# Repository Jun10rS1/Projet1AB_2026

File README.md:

# Projet1AB_2026
Notre projet comptage de personne

## Pense bete Git

```bash
git pull
# travail travail travail
git status
git add .
git commit -m "texte intelligent"
git push
```

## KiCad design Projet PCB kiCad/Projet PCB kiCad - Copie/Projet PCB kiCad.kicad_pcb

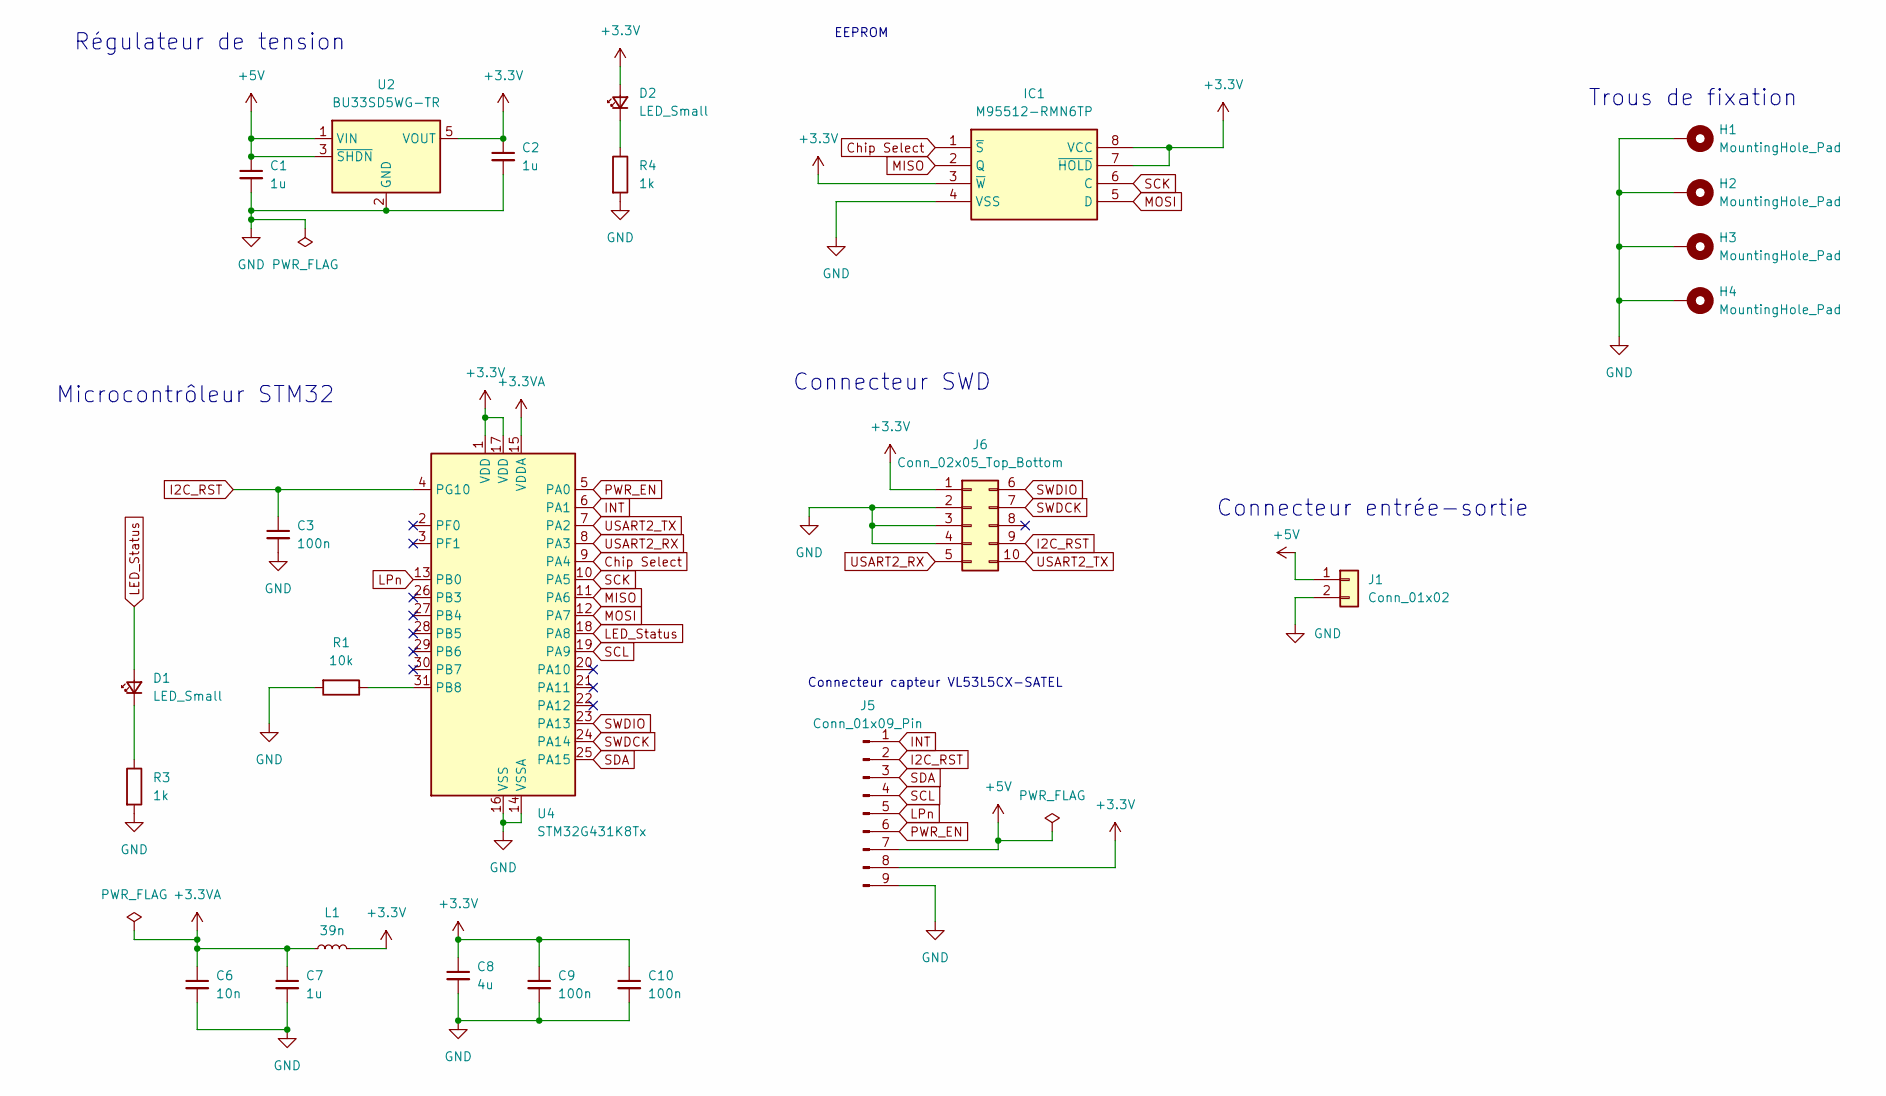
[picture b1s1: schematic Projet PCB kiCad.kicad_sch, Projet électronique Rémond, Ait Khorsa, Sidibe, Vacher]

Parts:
C1, C2, C7: 1u; C_0603_1608Metric_Pad1.08x0.95mm_HandSolder
C3, C9, C10: 100n; C_0603_1608Metric_Pad1.08x0.95mm_HandSolder
C6: 10n; C_0603_1608Metric_Pad1.08x0.95mm_HandSolder
C8: 4u; C_0603_1608Metric_Pad1.08x0.95mm_HandSolder
D1, D2: LED_Small; LED_0402_1005Metric_Pad0.77x0.64mm_HandSolder
H1, H2, H3, H4: MountingHole_Pad; MountingHole_3.2mm_M3_DIN965_Pad
IC1: M95512-RMN6TP; SOIC-8_3.9x4.9mm_P1.27mm; Mouser Part Number 511-M95512-RMN6TP
J1: Conn_01x02; JST_XH_B2B-XH-A_1x02_P2.50mm_Vertical
J5: Conn_01x09_Pin; PinSocket_1x09_P2.54mm_Vertical
J6: Conn_02x05_Top_Bottom; PinHeader_2x05_P2.54mm_Vertical
L1: 39n; L_0805_2012Metric_Pad1.05x1.20mm_HandSolder
R1: 10k; R_0402_1005Metric_Pad0.72x0.64mm_HandSolder
R3, R4: 1k; R_0402_1005Metric_Pad0.72x0.64mm_HandSolder
U2: BU33SD5WG-TR; SOT-23-5
U4: STM32G431K8Tx; LQFP-32_7x7mm_P0.8mm

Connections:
+3.3V: C2.1, C8.1, C9.1, C10.1, D2.2 (A), IC1.3 (~W), IC1.7 (~HOLD), IC1.8 (VCC), J5.8, J6.1, L1.2, U2.5 (VOUT), U4.1 (VDD), U4.17 (VDD)
+3.3VA: C6.1, C7.1, L1.1, U4.15 (VDDA)
+5V: C1.1, J1.1, J5.7, U2.1 (VIN), U2.3 (~SHDN)
Chip Select: IC1.1 (~S), U4.9 (PA4)
GND: C1.2, C2.2, C3.2, C6.2, C7.2, C8.2, C9.2, C10.2, H1.1, H2.1, H3.1, H4.1, IC1.4 (VSS), J1.2, J5.9, J6.2, J6.3, J6.4, R1.2, R3.2, R4.2, U2.2 (GND), U4.14 (VSSA), U4.16 (VSS), U4.32 (VSS)
I2C_RST: C3.1, J5.2, J6.9, U4.4 (PG10)
INT: J5.1, U4.6 (PA1)
LED_Status: D1.2 (A), U4.18 (PA8)
LPn: J5.5, U4.13 (PB0)
MISO: IC1.2 (Q), U4.11 (PA6)
MOSI: IC1.5 (D), U4.12 (PA7)
unnamed: D1.1 (K), R3.1
unnamed: D2.1 (K), R4.1
unnamed: R1.1, U4.31 (PB8)
PWR_EN: J5.6, U4.5 (PA0)
SCK: IC1.6 (C), U4.10 (PA5)
SCL: J5.4, U4.19 (PA9)
SDA: J5.3, U4.25 (PA15)
SWDCK: J6.7, U4.24 (PA14)
SWDIO: J6.6, U4.23 (PA13)
USART2_RX: J6.5, U4.8 (PA3)
USART2_TX: J6.10, U4.7 (PA2)

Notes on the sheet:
Trous de fixation
Connecteur entrée-sortie
Microcontrôleur STM32
Connecteur SWD
Régulateur de tension
EEPROM
Connecteur capteur VL53L5CX-SATEL

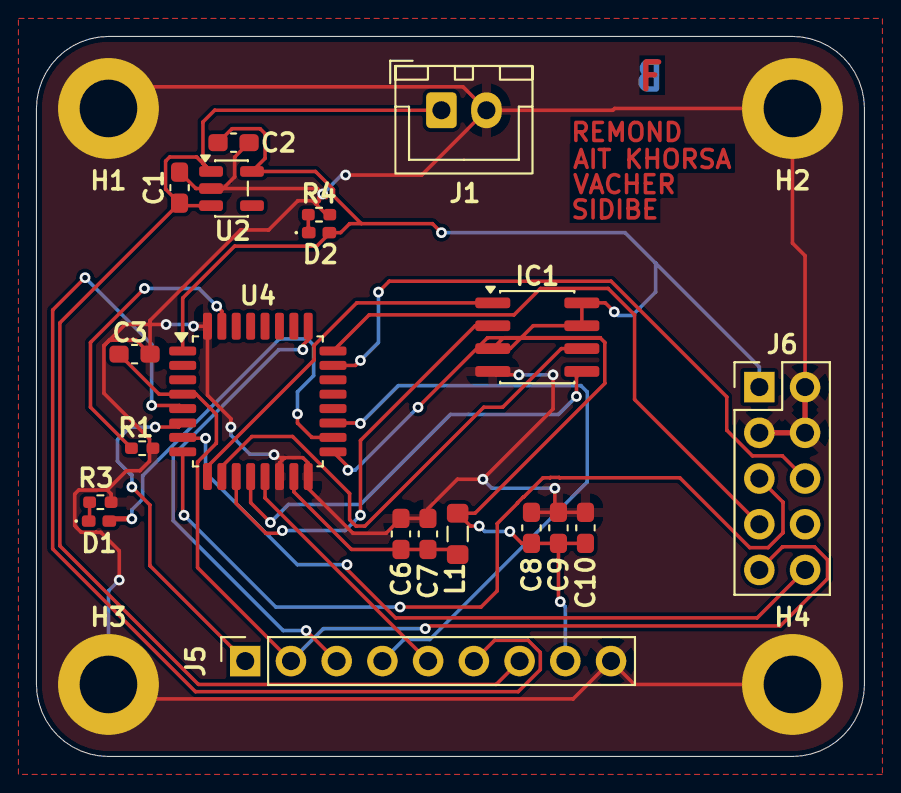
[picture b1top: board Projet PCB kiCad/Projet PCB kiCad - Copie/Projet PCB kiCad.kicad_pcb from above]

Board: 4 copper layers, 46.0 x 40.0 mm, 24 parts (0 on the bottom side), 22 nets.

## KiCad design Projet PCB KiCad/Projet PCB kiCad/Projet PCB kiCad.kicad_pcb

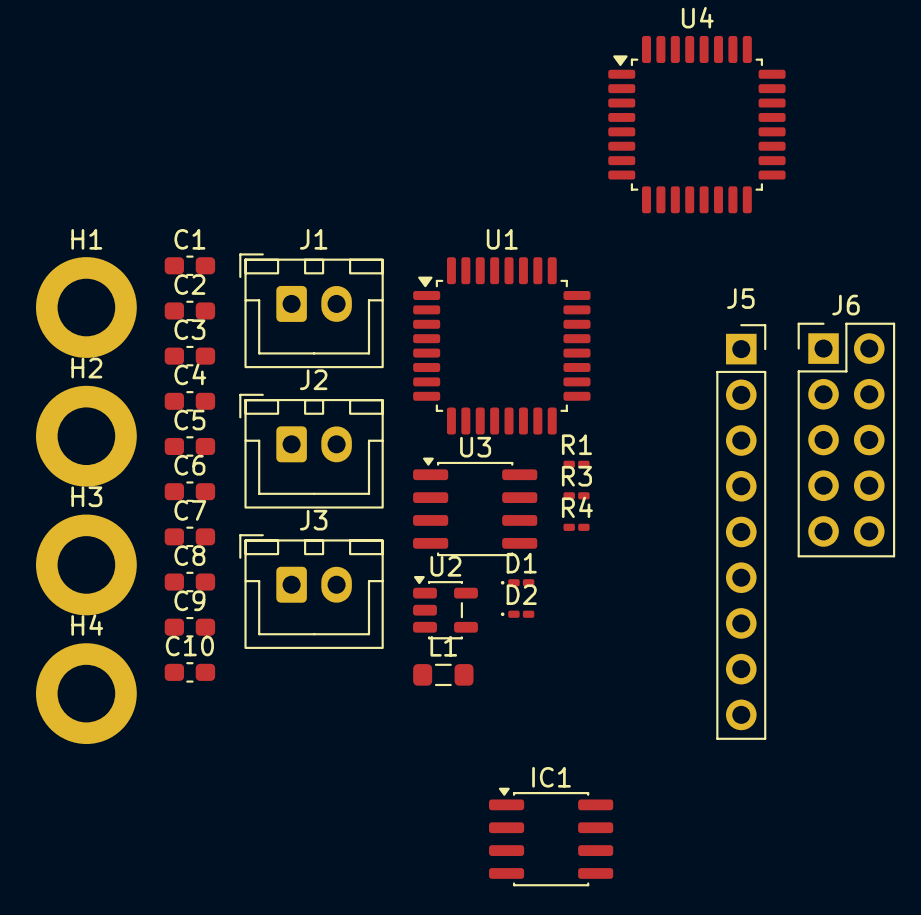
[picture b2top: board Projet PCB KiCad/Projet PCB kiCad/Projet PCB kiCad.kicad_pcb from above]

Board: 2 copper layers, 30 parts (0 on the bottom side), 19 nets, no tracks yet.

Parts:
C1, C2, C7: 1u; C_0603_1608Metric_Pad1.08x0.95mm_HandSolder
C3, C4, C9, C10: 100n; C_0603_1608Metric_Pad1.08x0.95mm_HandSolder
C5: 10u; C_0603_1608Metric_Pad1.08x0.95mm_HandSolder
C6: 10n; C_0603_1608Metric_Pad1.08x0.95mm_HandSolder
C8: 4u; C_0603_1608Metric_Pad1.08x0.95mm_HandSolder
D1, D2: LED_Small; LED_0201_0603Metric_Pad0.64x0.40mm_HandSolder
H1, H2, H3, H4: MountingHole_Pad; MountingHole_3.2mm_M3_DIN965_Pad
IC1: M95512-RMN6TP; SOIC-8_3.9x4.9mm_P1.27mm
J1, J2, J3: Conn_01x02; JST_XH_B2B-XH-A_1x02_P2.50mm_Vertical
J5: Conn_01x09_Pin; PinSocket_1x09_P2.54mm_Vertical
J6: Conn_02x05_Top_Bottom; PinHeader_2x05_P2.54mm_Vertical
L1: 39n; L_0805_2012Metric_Pad1.05x1.20mm_HandSolder
R1: 10k; R_0201_0603Metric_Pad0.64x0.40mm_HandSolder
R3, R4: 1k; R_0201_0603Metric_Pad0.64x0.40mm_HandSolder
U1: STM32L021K4Tx; LQFP-32_7x7mm_P0.8mm
U2: BU33SD5WG-TR; SOT-23-5
U3: MCP4801; SOIC-8_3.9x4.9mm_P1.27mm
U4: STM32G431K8Tx; LQFP-32_7x7mm_P0.8mm

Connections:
+3.3V: C2.1, C8.1, C9.1, C10.1, D2.2 (A), J6.1, L1.2, U1.1 (VDD), U1.17 (VDD), U2.5 (VOUT), U4.1 (VDD), U4.17 (VDD)
+3.3VA: C4.1, C5.1, C6.1, C7.1, L1.1, U1.5 (VDDA), U3.1 (Vdd), U3.6 (~SHDN), U4.15 (VDDA)
+5V: C1.1, J1.1, U2.1 (VIN), U2.3 (~SHDN)
ADC_IN1: J2.1, U1.7 (PA1), U4.6 (PA1)
DAC_OUT: J3.1, U3.8 (Vout)
DAC_nCS: U1.10 (PA4), U3.2 (~CS)
DAC_nLDAC: U1.9 (PA3), U3.5 (~LDAC)
GND: C1.2, C2.2, C3.2, C4.2, C5.2, C6.2, C7.2, C8.2, C9.2, C10.2, H1.1, H2.1, H3.1, H4.1, J1.2, J2.2, J3.2, J5.9, J6.2, J6.3, J6.4, R1.2, R3.2, R4.2, U1.16 (VSS), U1.32 (VSS), U2.2 (GND), U3.7 (Vss), U4.14 (VSSA), U4.16 (VSS), U4.32 (VSS)
LED_Status: D1.2 (A), U1.18 (PA8), U4.18 (PA8)
unnamed: D1.1 (K), R3.1
unnamed: D2.1 (K), R4.1
unnamed: R1.1, U4.31 (PB8)
PG10: C3.1, J6.9, U4.4 (PG10)
SPI1_MOSI: U1.13 (PA7), U3.4 (SDI)
SPI1_SCK: U1.11 (PA5), U3.3 (SCK)
SWDCK: J6.7, U1.24 (PA14), U4.24 (PA14)
SWDIO: J6.6, U1.23 (PA13), U4.23 (PA13)
USART2_RX: J6.5, U1.6 (PA0), U4.5 (PA0)
USART2_TX: J6.10, U1.8 (PA2), U4.7 (PA2)

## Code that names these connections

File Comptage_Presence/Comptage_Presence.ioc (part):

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Mcu.Name=STM32L476R(C-E-G)Tx
Mcu.Package=LQFP64
Mcu.UserName=STM32L476RGTx
PA13\ (JTMS-SWDIO).GPIOParameters=GPIO_Label
PA13\ (JTMS-SWDIO).GPIO_Label=TMS
PA13\ (JTMS-SWDIO).Mode=Serial_Wire
PA13\ (JTMS-SWDIO).Signal=SYS_JTMS-SWDIO
PA14\ (JTCK-SWCLK).GPIOParameters=GPIO_Label
PA14\ (JTCK-SWCLK).GPIO_Label=TCK
PA14\ (JTCK-SWCLK).Mode=Serial_Wire
PA14\ (JTCK-SWCLK).Signal=SYS_JTCK-SWCLK
PA2.GPIOParameters=GPIO_Speed,GPIO_PuPd,GPIO_Label,GPIO_Mode
PA2.GPIO_Label=USART_TX
PA2.GPIO_Mode=GPIO_MODE_AF_PP
PA2.GPIO_PuPd=GPIO_NOPULL
PA2.GPIO_Speed=GPIO_SPEED_FREQ_VERY_HIGH
PA2.Mode=Asynchronous
PA2.Signal=USART2_TX
PA3.GPIOParameters=GPIO_Speed,GPIO_PuPd,GPIO_Label,GPIO_Mode
PA3.GPIO_Label=USART_RX
PA3.GPIO_Mode=GPIO_MODE_AF_PP
PA3.GPIO_PuPd=GPIO_NOPULL
PA3.GPIO_Speed=GPIO_SPEED_FREQ_VERY_HIGH
PA3.Mode=Asynchronous
PA3.Signal=USART2_RX
PA4.Signal=GPIO_Output
PA5.Mode=Full_Duplex_Master
PA5.Signal=SPI1_SCK
PA6.Mode=Full_Duplex_Master
PA6.Signal=SPI1_MISO
PA7.Mode=Full_Duplex_Master
PA7.Signal=SPI1_MOSI
PB10.Mode=I2C
PB10.Signal=I2C2_SCL
PB11.Mode=I2C
PB11.Signal=I2C2_SDA
PB3\ (JTDO-TRACESWO).GPIOParameters=GPIO_Label
PB3\ (JTDO-TRACESWO).GPIO_Label=SWO
PB3\ (JTDO-TRACESWO).Signal=SYS_JTDO-SWO
PB8.Signal=GPIO_Output
PB9.Signal=I2C1_SDA
PC13.GPIOParameters=GPIO_PuPd,GPIO_Label,GPIO_ModeDefaultEXTI
PC13.GPIO_Label=B1 [Blue PushButton]
PC13.GPIO_ModeDefaultEXTI=GPIO_MODE_IT_FALLING
PC13.GPIO_PuPd=GPIO_NOPULL
PC13.Signal=GPXTI13
PC14-OSC32_IN\ (PC14).Mode=LSE-External-Oscillator
PC14-OSC32_IN\ (PC14).Signal=RCC_OSC32_IN
PC15-OSC32_OUT\ (PC15).Mode=LSE-External-Oscillator
PC15-OSC32_OUT\ (PC15).Signal=RCC_OSC32_OUT
PH0-OSC_IN\ (PH0).Signal=RCC_OSC_IN
PH1-OSC_OUT\ (PH1).Signal=RCC_OSC_OUT
RCC.HSE_VALUE=8000000
RCC.SYSCLKFreq_VALUE=80000000
RCC.SYSCLKSource=RCC_SYSCLKSOURCE_PLLCLK
board=NUCLEO-L476RG
boardIOC=true

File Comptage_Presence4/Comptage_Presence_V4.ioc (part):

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Mcu.Name=STM32G441KBTx
Mcu.Package=LQFP32
Mcu.UserName=STM32G441KBTx
PA1.GPIOParameters=GPIO_PuPd,GPIO_Label,GPIO_ModeDefaultEXTI
PA1.GPIO_Label=VL53_INT
PA1.GPIO_ModeDefaultEXTI=GPIO_MODE_IT_FALLING
PA1.GPIO_PuPd=GPIO_PULLUP
PA1.Signal=GPXTI1
PA13.Mode=Serial_Wire
PA13.Signal=SYS_JTMS-SWDIO
PA14.Mode=Serial_Wire
PA14.Signal=SYS_JTCK-SWCLK
PA8.Mode=I2C
PA8.Signal=I2C2_SDA
PA9.Mode=I2C
PA9.Signal=I2C2_SCL
PB0.GPIOParameters=GPIO_Label
PB0.GPIO_Label=VL53_LPn
PB0.Signal=GPIO_Output
RCC.HSE_VALUE=8000000
RCC.SYSCLKFreq_VALUE=160000000
RCC.SYSCLKSource=RCC_SYSCLKSOURCE_PLLCLK
board=custom

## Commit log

2026-02-09 premier push
2026-02-09 schema kicad
2026-02-16 ajout des rapports de fin de séance
2026-02-16 kicad
2026-02-16 ajout du kicad
2026-02-16 kicad eeprom
2026-02-16 ajout présentation projet du prof
2026-02-16 ajout des datasheet
2026-02-16 maj datasheet
2026-02-16 Kicad fin schema
2026-02-18 test
2026-03-09 rapport seance 3
2026-03-09 repertoire DRC
2026-03-09 fin de kicad
2026-03-16 rapport séance 4
2026-04-26 Ajout d'un nouveau dossier avec .gitkeep
2026-05-09 nouveau commit
2026-05-11 rapport 8
2026-05-11 rapport séance 8
2026-05-14 nouveau commit Comptage_Presence3
2026-05-15 Commit du Comptage_Presence4
2026-05-18 rapport finale
